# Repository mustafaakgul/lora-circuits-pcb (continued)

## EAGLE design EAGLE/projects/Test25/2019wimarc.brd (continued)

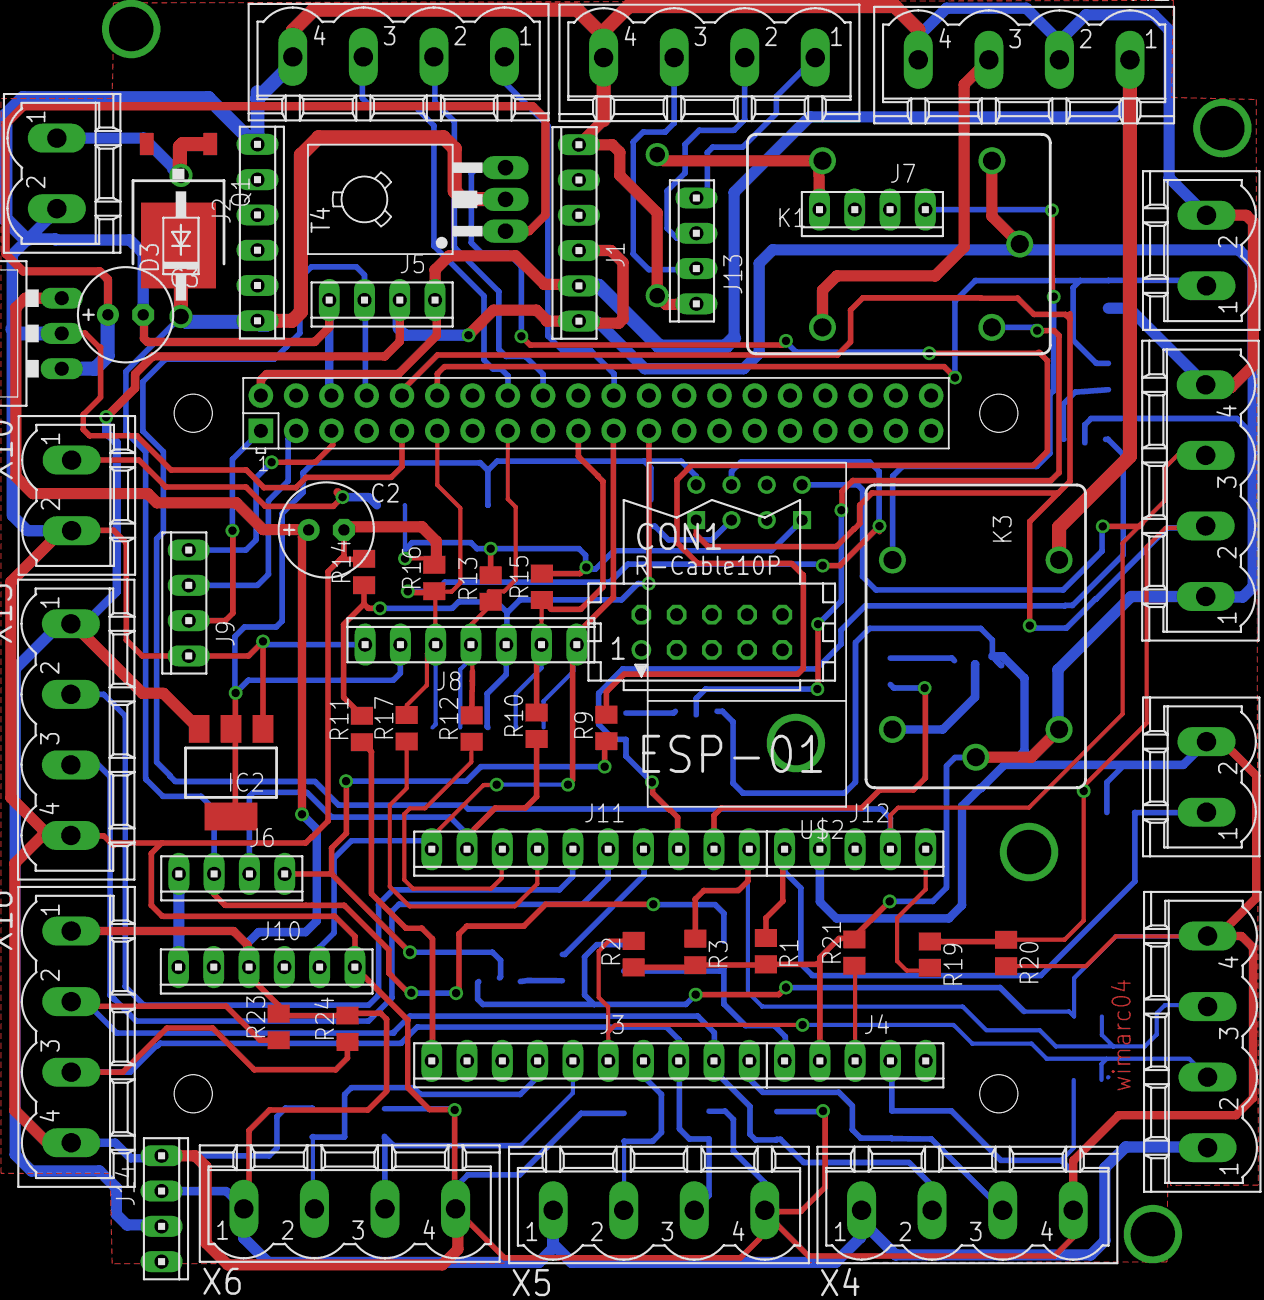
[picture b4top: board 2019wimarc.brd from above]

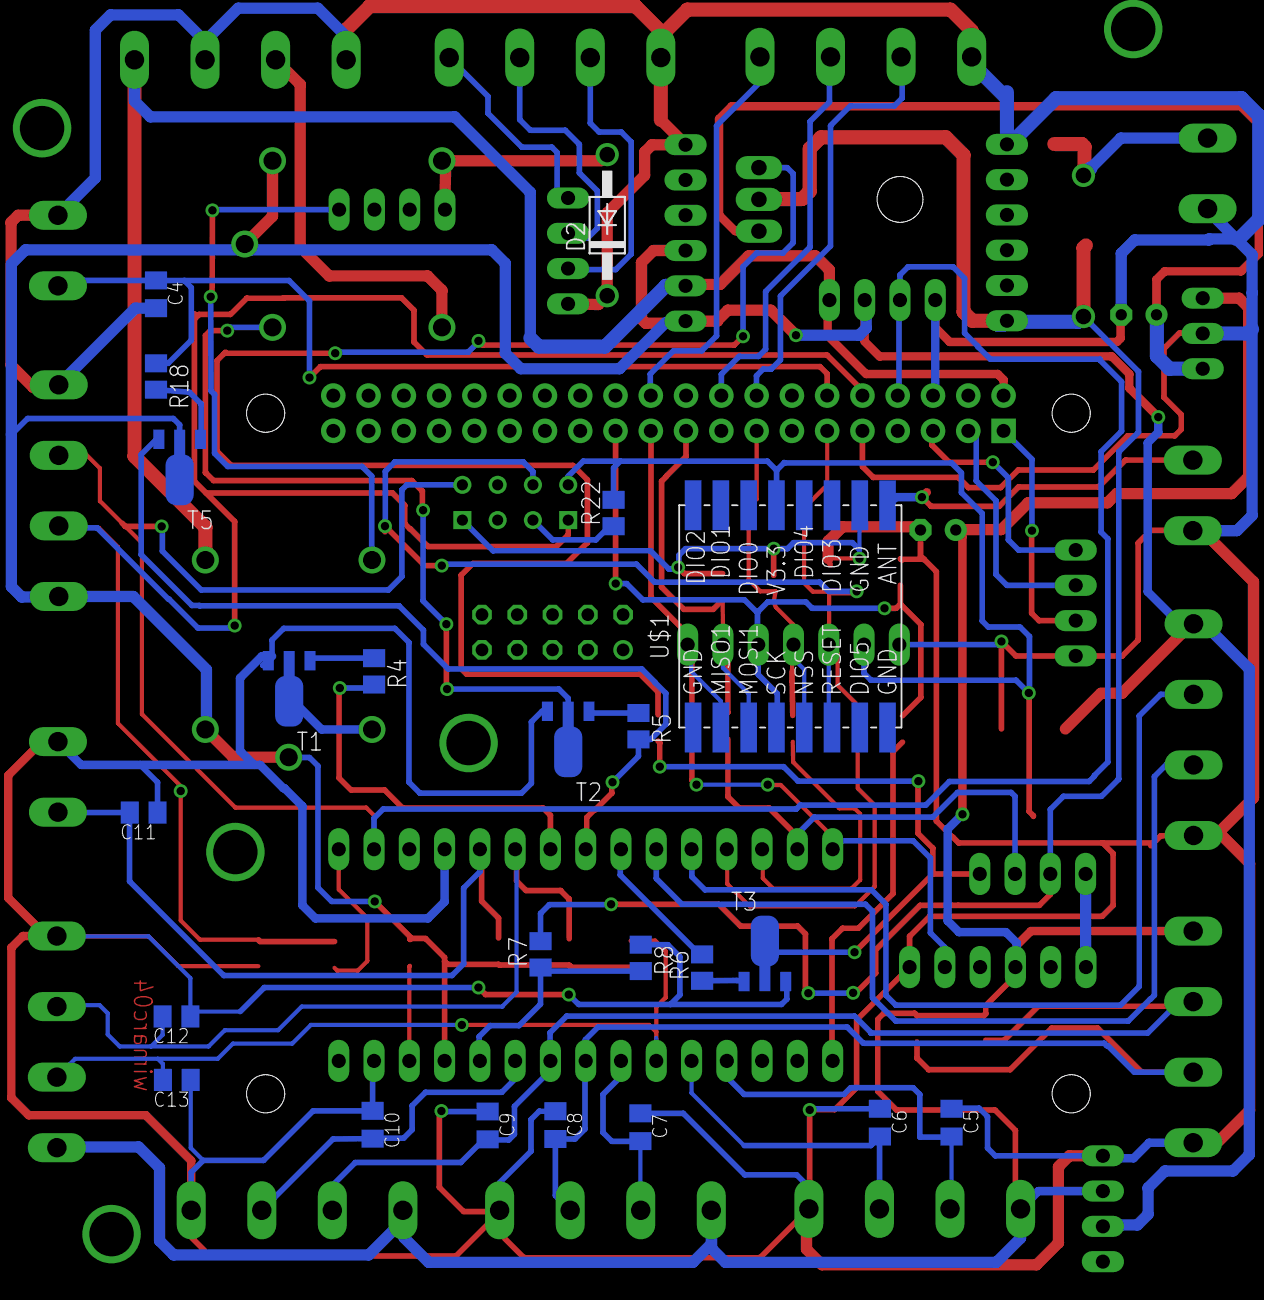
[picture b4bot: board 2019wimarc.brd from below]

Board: 2 copper layers, 80 parts (23 on the bottom side), 60 nets.

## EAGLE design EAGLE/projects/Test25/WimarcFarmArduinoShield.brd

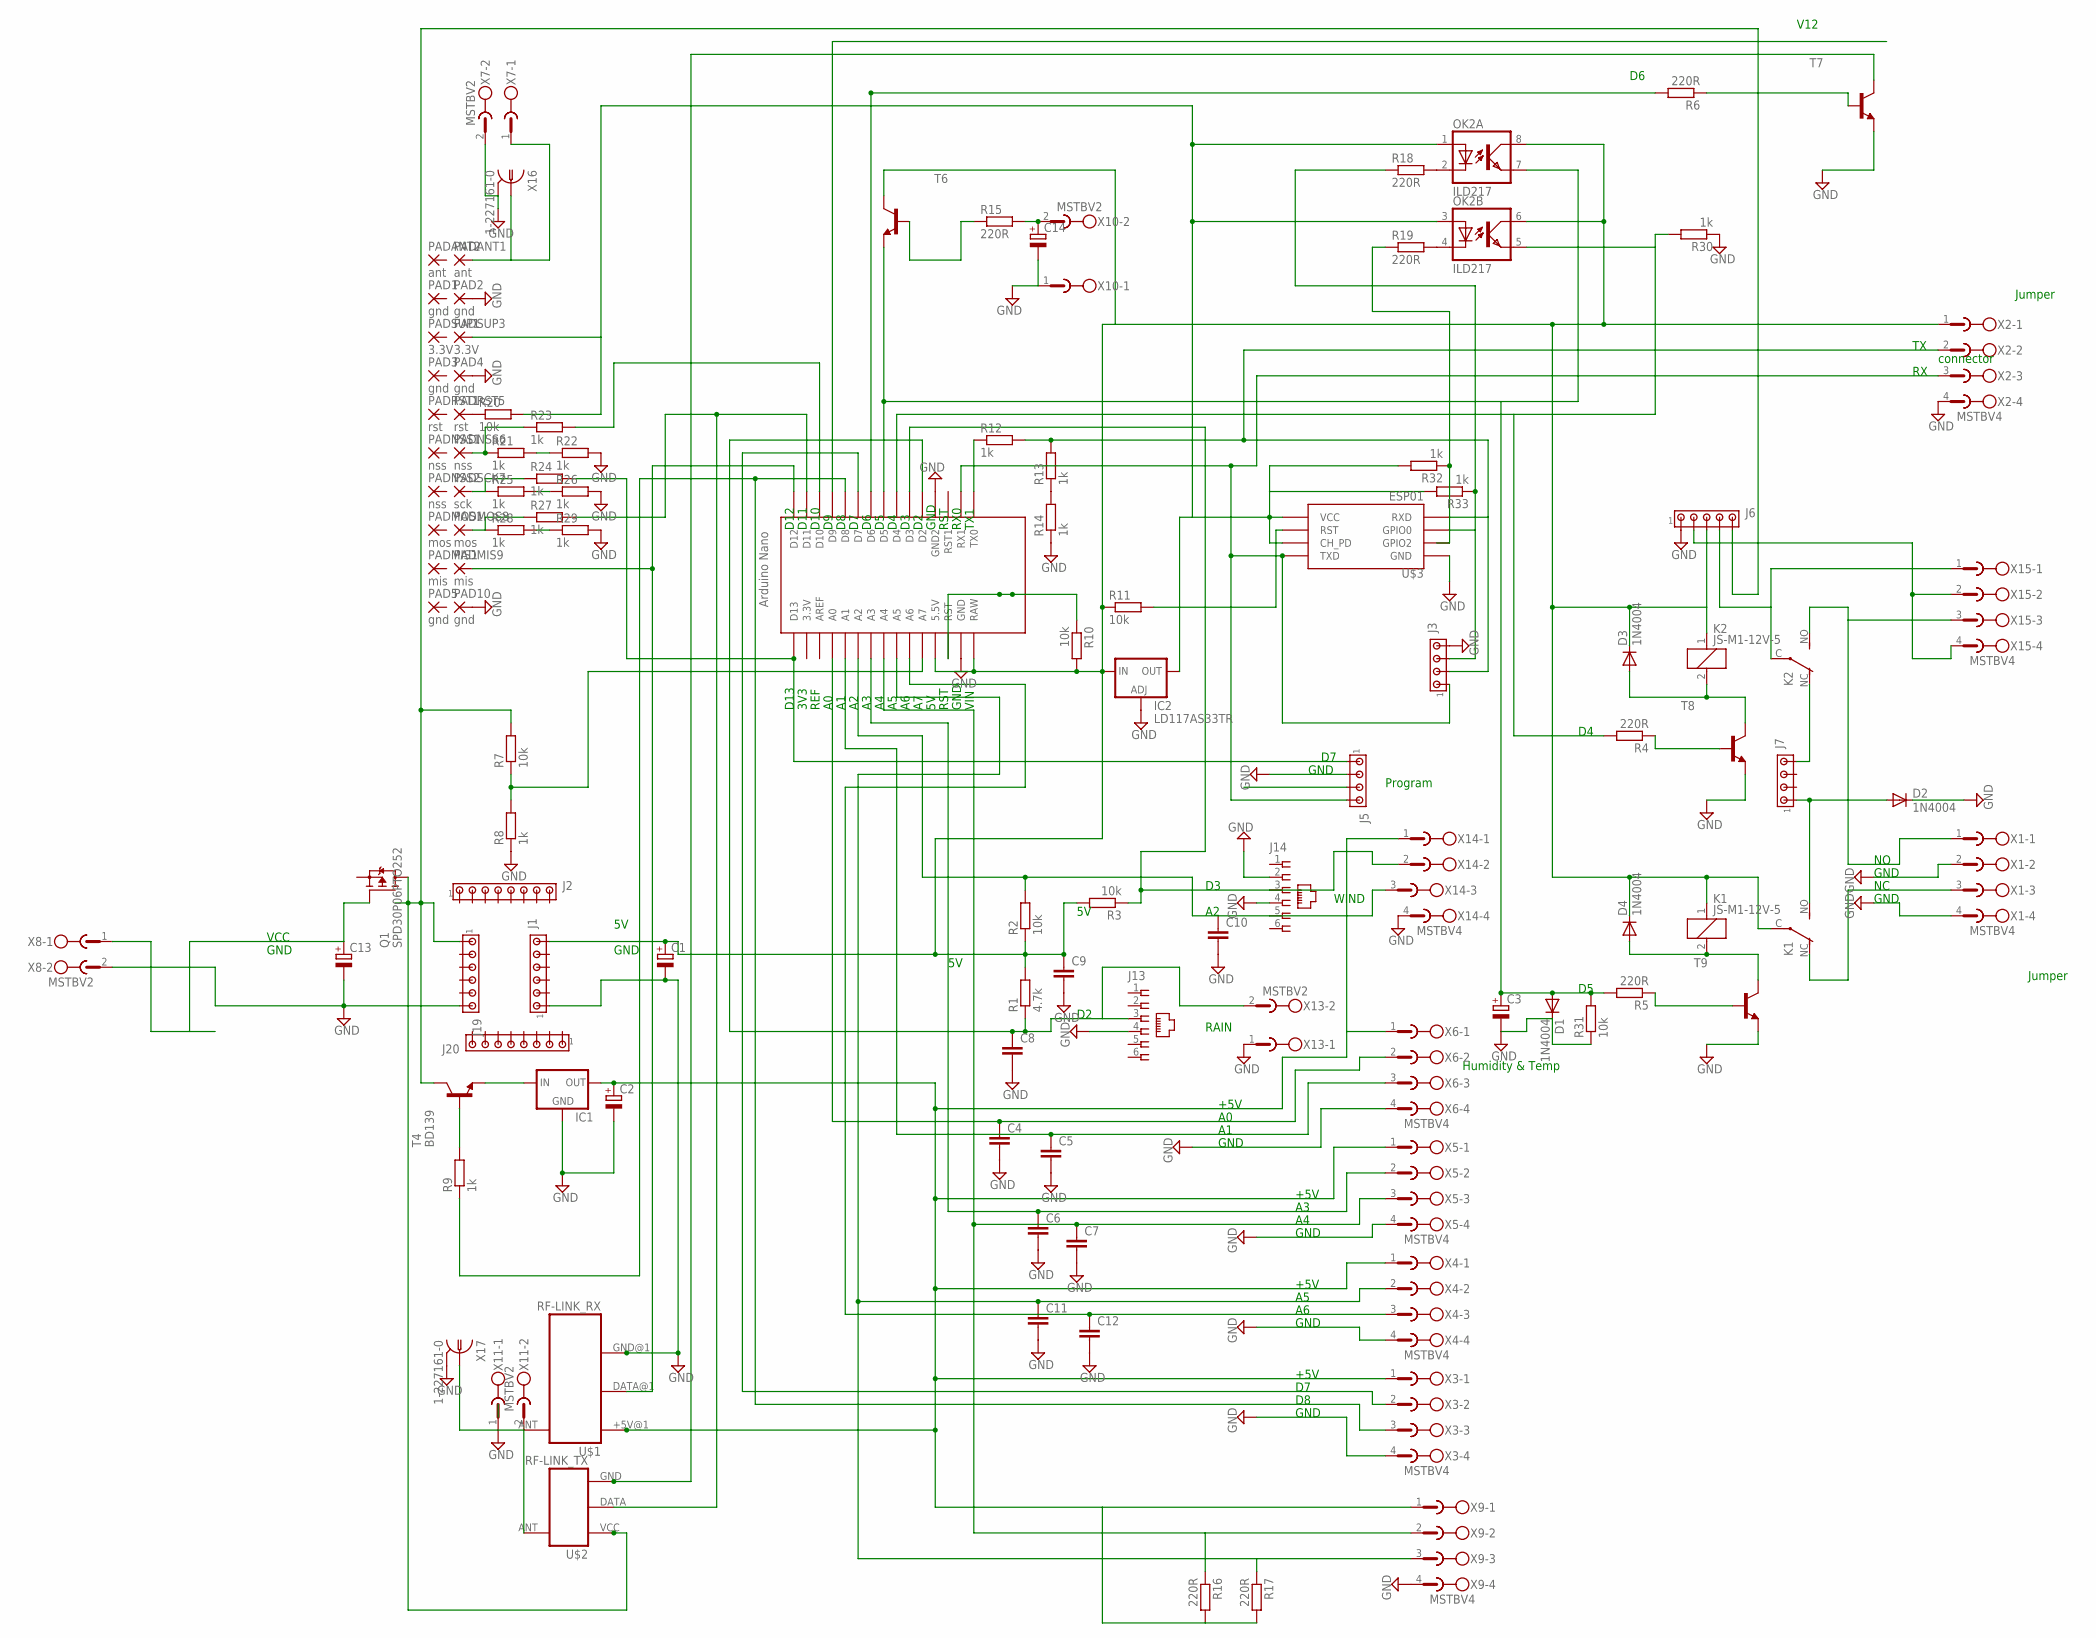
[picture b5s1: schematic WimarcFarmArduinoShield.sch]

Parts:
C1, C3, C13, C14: CPOL-EUE2.5-7; E2,5-7
C2: CPOL-EUE3.5-10; E3,5-10
C4, C5, C6, C7, C8, C9, C10, C11, C12: C-EUC0805K; C0805K
D1, D2, D3, D4: 1N4004; DO41-10
IC1: 78XXS
IC2: LD117AS33TR; SOT223
J1, J19: MTA06-100; 10X06MTA
J2, J20: MTA08-100; 10X08MTA
J3, J5, J7: MTA04-100; 10X04MTA
J6: MTA05-100; 10X05MTA
J13, J14: 520250-3
K1, K2: JS-M1-12V-5; JS-M
OK2: ILD217; SOIC08
PAD1, PAD2, PAD3, PAD4, PAD5, PAD10: gnd; 1,6/0,8
PADANT1, PADANT2: ant; 1,6/0,8
PADMIS1, PADMIS9: mis; 1,6/0,8
PADMOS1, PADMOS8: mos; 1,6/0,8
PADNSS1, PADNSS2, PADNSS6: nss; 1,6/0,8
PADRST1, PADRST5: rst; 1,6/0,8
PADSCK7: sck; 1,6/0,8
PADSUP1, PADSUP3: 3.3V; 1,6/0,8
Q1: SPD30P06PTO252; TO252
R1: 4.7k; M0805
R2, R3, R7, R10, R11, R20, R31: 10k; M0805
R4, R5, R6, R15, R16, R17, R18, R19: 220R; M0805
R8, R9, R12, R13, R14, R21, R22, R23, R24, R25, R26, R27, R28, R29, R30, R32, R33: 1k; M0805
T4: BD139; TO126
T6, T7, T8, T9: -NPN-SOT89-BCE; SOT89-BCE
U$1: RF-LINK_RX
U$2: RF-LINK_TX
U$3: ESP01
U$4: NANO
X1, X2, X3, X4, X5, X6, X9, X14, X15: MSTBV4
X7, X8, X10, X11, X13: MSTBV2
X16, X17: 1-227161-0; AMP_227161

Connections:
GND: C1.-, C2.-, C3.-, C4.2, C5.2, C6.2, C7.2, C8.2, C9.2, C10.2, C11.2, C12.2, C13.-, C14.-, D1.C, D2.C, IC1.GND, IC2.1 (ADJ), J1.1, J3.4, J5.2, J6.1, J13.4, J14.2, J14.4, J19.6, PAD2.1, PAD4.1, PAD10.1, R8.1, R14.1, R22.2, R26.2, R29.2, R30.1, R31.1, T7.E, T8.E, T9.E, U$1.GND@1 (GND), U$3.GND, U$4.GND, U$4.GND1 (GND2), X1.2, X1.4, X2.4, X3.4, X4.4, X5.4, X6.4, X7.2, X8.2, X9.4, X10.1, X11.1, X13.1, X14.4, X16.2, X17.2
unnamed: C4.1, U$4.A0, X6.2
unnamed: C8.1, J13.3, R1.1, U$4.D2, X13.2
unnamed: J14.3, R3.1, U$4.D3, X14.2
unnamed: J7.4, K2.NC (O)
unnamed: J5.1, R24.2, U$4.D13
unnamed: C13.+, Q1.1 (G), X8.1
unnamed: J3.1, J5.4, U$3.TX (TXD), U$4.RX1, X2.3
unnamed: U$1.ANT, U$2.ANT, X11.2, X17.1
unnamed: PADMIS9.1, U$1.DATA@1 (DATA), U$4.D12
unnamed: J3.3, R18.1, R33.1, U$3.GPIO0
unnamed: C5.1, U$4.A1, X6.3
unnamed: C6.1, U$4.A3, X5.2
unnamed: C7.1, R16.1, U$4.A4, X5.3, X9.2
unnamed: C11.1, R17.1, U$4.A5, X4.2, X9.3
unnamed: C12.1, U$4.A6, X4.3
unnamed: U$4.D7, X3.2
unnamed: R11.2, U$3.RST
unnamed: D3.A, K2.2, T8.C
unnamed: C2.+, IC1.OUT, R16.2, R17.2, U$1.+5V@1 (+5V), X3.1, X4.1, X5.1, X6.1, X9.1, X14.1
unnamed: R4.1, T8.B
unnamed: D4.A, K1.2, T9.C
unnamed: R5.1, T9.B
unnamed: K1.NC (O), X1.3
unnamed: T7.C, U$2.GND
unnamed: R27.2, U$2.DATA, U$4.D11
unnamed: K2.NO (S), X1.1, X15.3
unnamed: R7.1, R8.2, U$4.A7
unnamed: R6.1, T7.B
unnamed: OK2.5 (EMIT), R4.2, R30.2, U$4.D4
unnamed: C3.+, D1.A, OK2.7 (EMIT), R5.2, R31.2, T6.E, U$4.D5
unnamed: R6.2, U$4.D6
unnamed: R12.1, U$4.TX0
unnamed: D2.A, J7.1, K1.NO (S)
unnamed: R23.2, U$4.D10
unnamed: IC1.IN, T4.1 (E)
unnamed: R9.2, T4.3 (B)
unnamed: R9.1, U$4.D8, X3.3
unnamed: R10.1, U$4.ICSP1, U$4.ICSP2, U$4.RST
unnamed: IC2.4 (OUT), OK2.1 (A), OK2.3 (A), PADSUP3.1, R20.2, R32.2, R33.2, U$3.CH_PD, U$3.VCC
unnamed: J3.2, R12.2, R13.2, U$3.RX (RXD), X2.2
unnamed: J6.4, K2.C, X15.1
unnamed: R15.1, T6.B
unnamed: C14.+, R15.2, X10.2
unnamed: R19.1, R32.1, U$3.GPIO2
unnamed: OK2.2 (C), R18.2
unnamed: R13.1, R14.2
unnamed: OK2.4 (C), R19.2
unnamed: J6.2, X15.2, X15.4
unnamed: C10.1, J14.5, R2.2, U$4.A2, X14.3
unnamed: PADSCK7.1, R24.1, R25.1
unnamed: PADRST5.1, R20.1
unnamed: PADNSS6.1, R21.1, R23.1
unnamed: R21.2, R22.1
unnamed: R25.2, R26.1
unnamed: PADMOS8.1, R27.1, R28.1
unnamed: R28.2, R29.1
unnamed: PADANT1.1, X7.1, X16.1
unnamed: C1.+, C9.1, D3.C, D4.C, IC2.3 (IN), J1.6, J6.3, K1.1, K1.C, K2.1, OK2.6 (COL), OK2.8 (COL), R1.2, R2.1, R3.2, R10.2, R11.1, T6.C, U$4.5V (5.5V), U$4.RAW, X2.1
SUPPLY: J6.5, J19.1, Q1.3 (D), R7.2, T4.2 (C), U$2.VCC (+5V)

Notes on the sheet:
D13
3V3
REF
RST
GND
VIN
TX1
RX0
D10
D11
D12
Program
WIND
RAIN
+5V
Humidity & Temp
Jumper
connector
VCC
V12

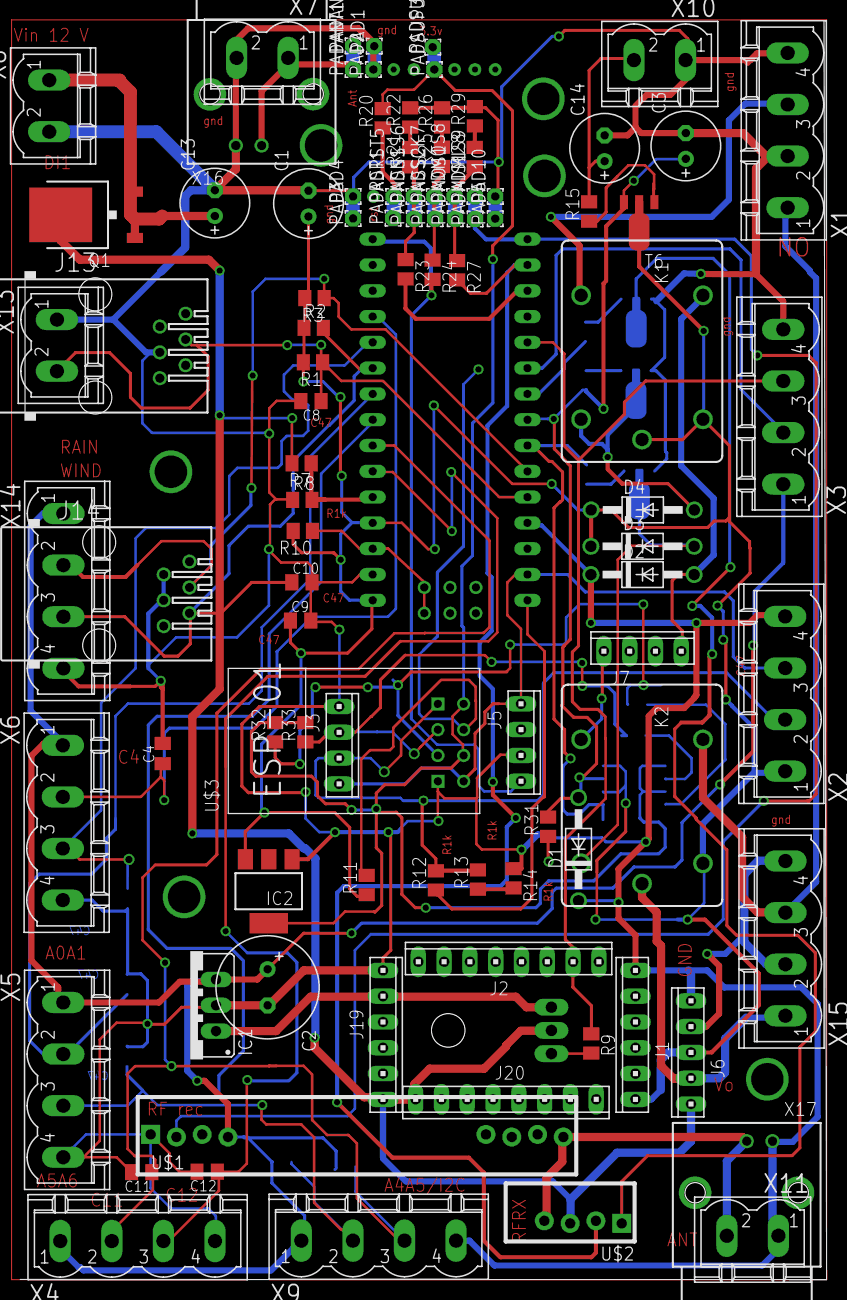
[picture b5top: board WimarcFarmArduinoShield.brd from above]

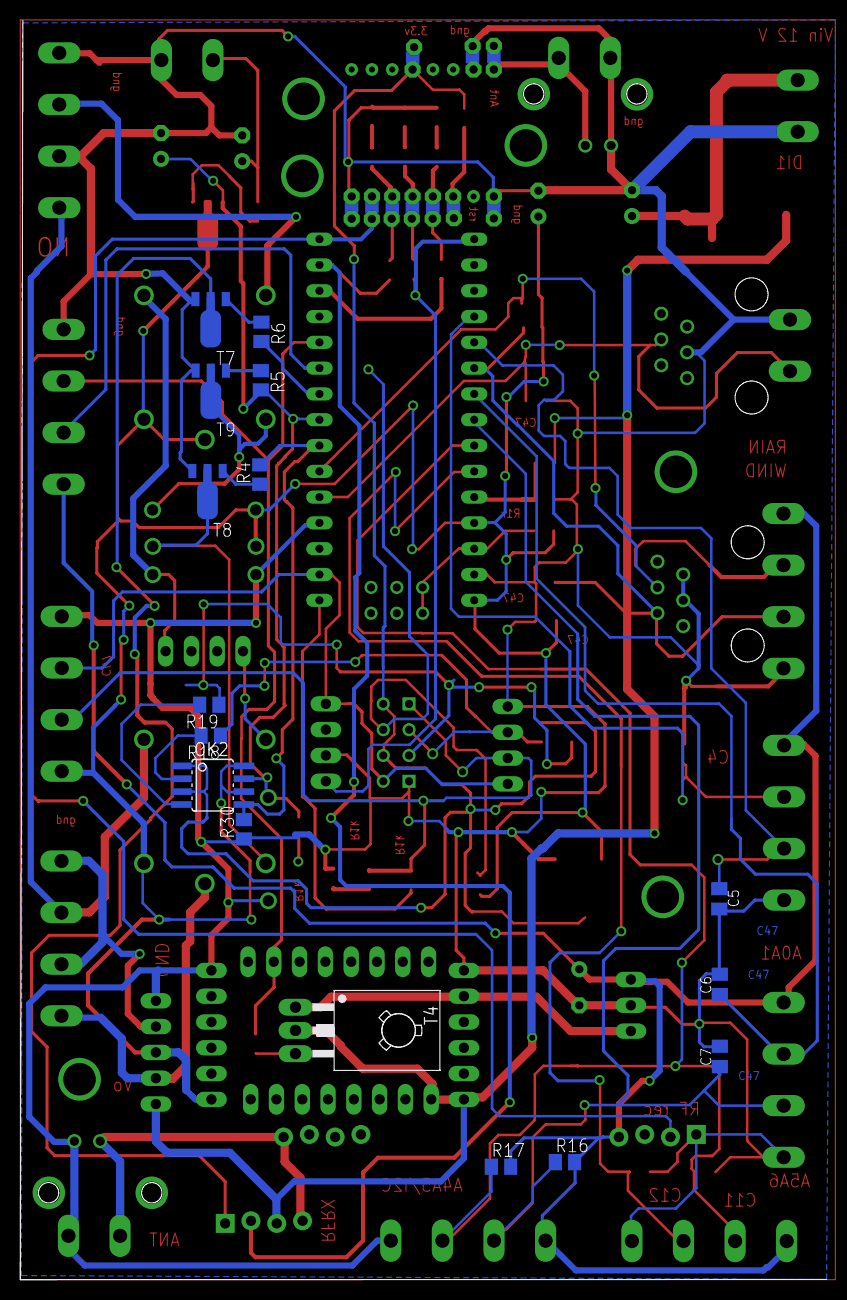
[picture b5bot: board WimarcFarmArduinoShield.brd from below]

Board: 2 copper layers, 79.4 x 124.0 mm, 112 parts (16 on the bottom side), 60 nets.
